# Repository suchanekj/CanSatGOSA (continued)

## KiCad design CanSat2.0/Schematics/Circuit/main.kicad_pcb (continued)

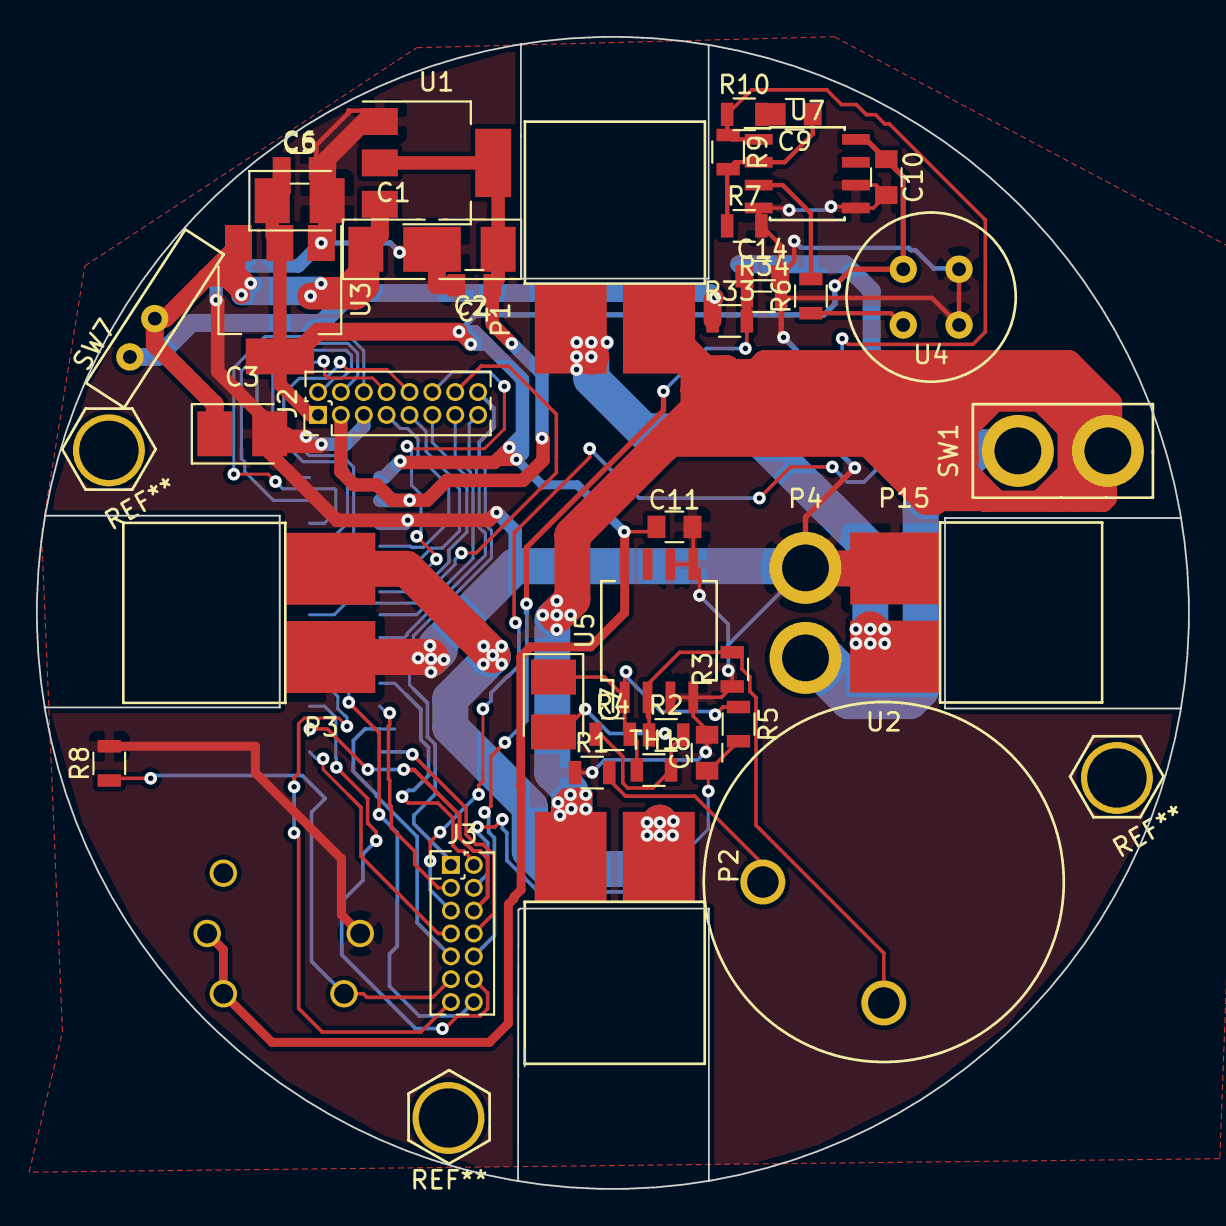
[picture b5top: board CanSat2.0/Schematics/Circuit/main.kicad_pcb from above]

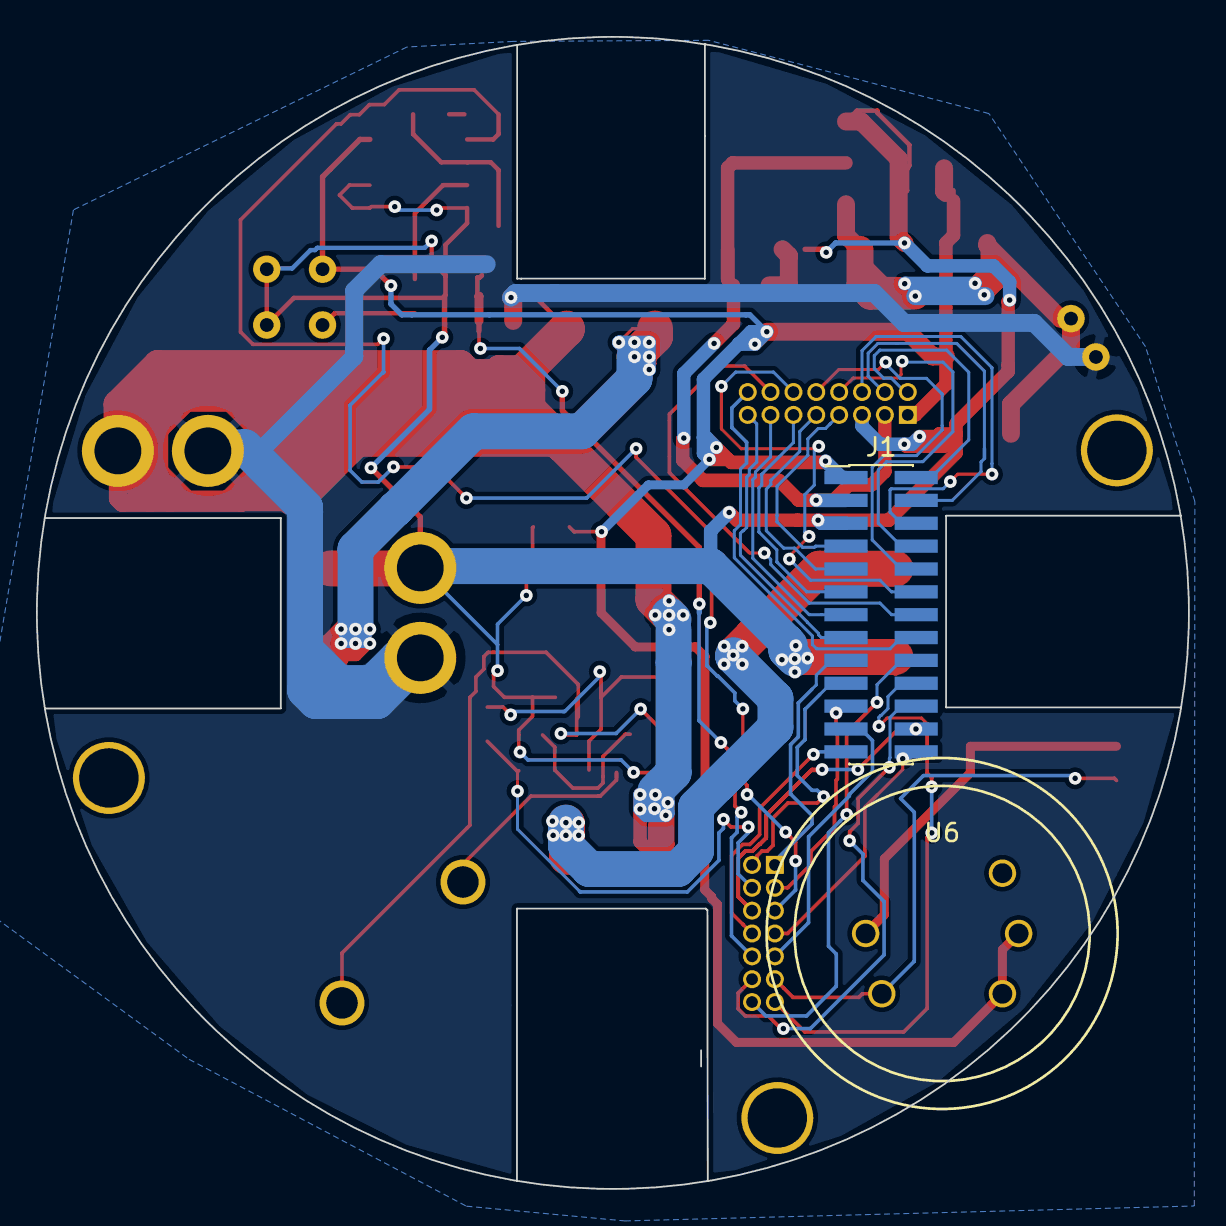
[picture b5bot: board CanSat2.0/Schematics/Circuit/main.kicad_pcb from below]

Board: 2 copper layers, 64.0 x 64.0 mm, 42 parts (2 on the bottom side), 43 nets.

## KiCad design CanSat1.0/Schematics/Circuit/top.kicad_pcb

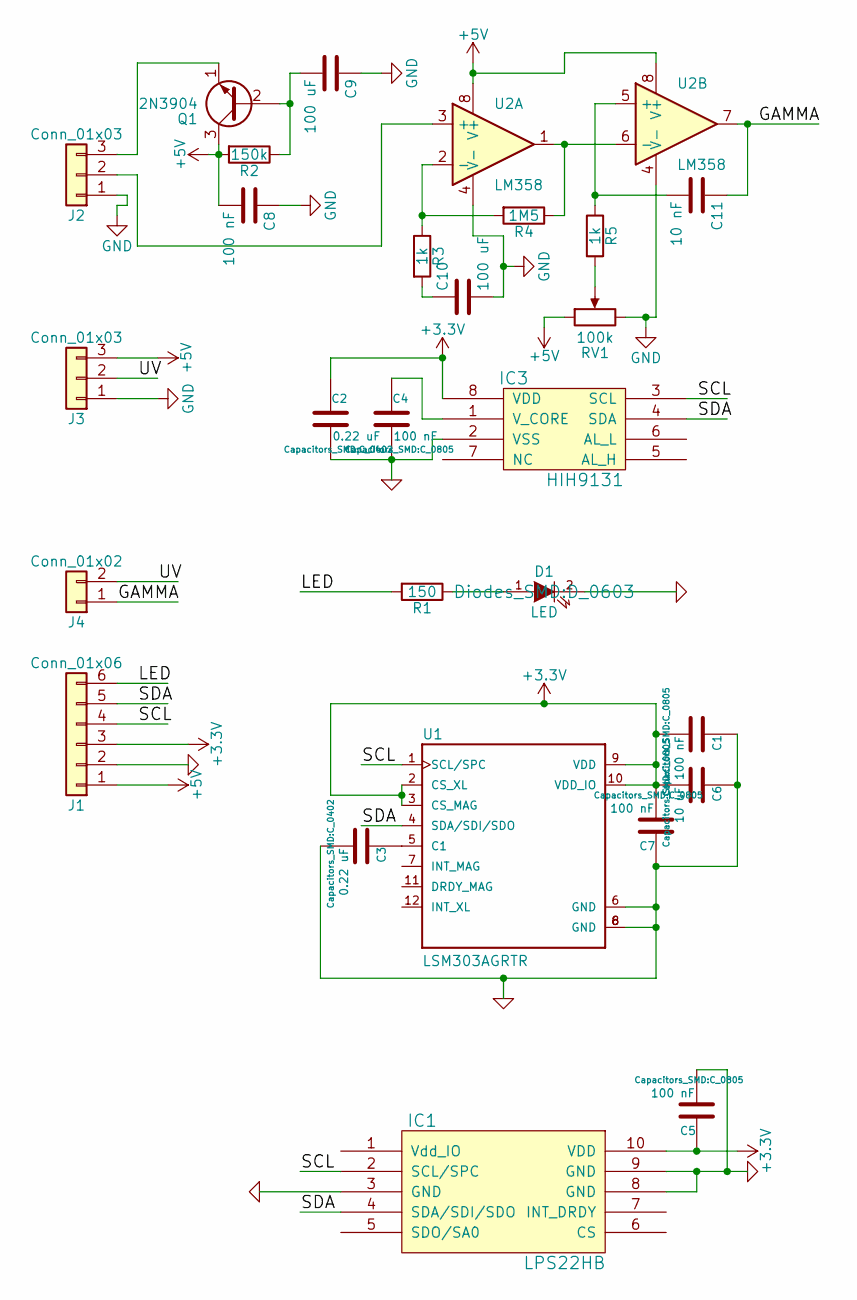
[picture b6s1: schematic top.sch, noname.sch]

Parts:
C1, C4, C5, C7, C8: 100 nF; C_0805
C2, C3: 0.22 uF; C_0402
C6: 10 uF; C_0805
C9, C10: 100 uF; CP_Tantalum_Case-A_EIA-3216-18_Reflow
C11: 10 nF; C_0603
D1: LED; D_0603
IC1: LPS22HB; LGA10R50P2X3_200X200X80
IC3: HIH9131; SOIC127P600X175-8N
J1: Conn_01x06; Pin_Header_Straight_1x06_Pitch1.27mm_SMD_Pin1Left
J2: Conn_01x03; MOLEX_PicoBlade_3
J3: Conn_01x03; Pin_Header_Straight_1x03_Pitch2.54mm
J4: Conn_01x02; MOLEX_PicoBlade_2
Q1: 2N3904; TO-92_Molded_Narrow
R1: 150; R_0805
R2: 150k; R_0603
R3, R5: 1k; R_0603
R4: 1M5; R_0603
RV1: 100k; Pin_Header_Straight_1x03_Pitch2.54mm
U1: LSM303AGRTR
U2: LM358; SOIC127P600X175-8N

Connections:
+3V3: C1.2, C2.1, C5.1, C6.2, C7.2, IC1.10 (VDD), IC3.8 (VDD), J1.3, U1.2 (CS_XL), U1.3 (CS_MAG), U1.9 (VDD), U1.10 (VDD_IO)
+5V: C8.2, J1.1, J3.3, Q1.3 (C), R2.2, RV1.1, U2.8 (V+)
/GAMMA: C11.1, J4.1, U2.7
/LED: J1.6, R1.2
/SCL: IC1.2 (SCL/SPC), IC3.3 (SCL), J1.4, U1.1 (SCL/SPC)
/SDA: IC1.4 (SDA/SDI/SDO), IC3.4 (SDA), J1.5, U1.4 (SDA/SDI/SDO)
/UV: J3.2, J4.2
GND: C1.1, C2.2, C3.2, C4.2, C5.2, C6.1, C7.1, C8.1, C9.1, C10.2, D1.2 (K), IC1.3 (GND), IC1.8 (GND), IC1.9 (GND), IC3.2 (VSS), J1.2, J2.1, J3.1, RV1.3, U1.6 (GND), U1.8 (GND), U2.4 (V-)
unnamed: C3.1, U1.5 (C1)
unnamed: C4.1, IC3.1 (V_CORE)
unnamed: C9.2, Q1.2 (B), R2.1
unnamed: C10.1, R3.2
unnamed: C11.2, R5.1, U2.5 (+)
unnamed: D1.1 (A), R1.1
unnamed: J2.2, U2.3 (+)
unnamed: J2.3, Q1.1 (E)
unnamed: R3.1, R4.2, U2.2 (-)
unnamed: R4.1, U2.1, U2.6 (-)
unnamed: R5.2, RV1.2

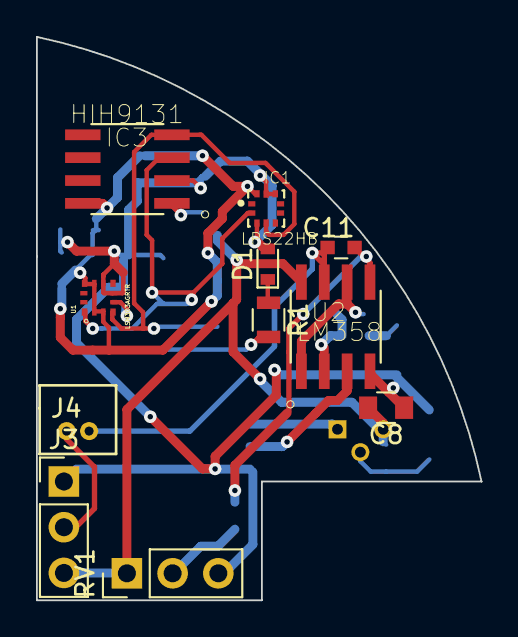
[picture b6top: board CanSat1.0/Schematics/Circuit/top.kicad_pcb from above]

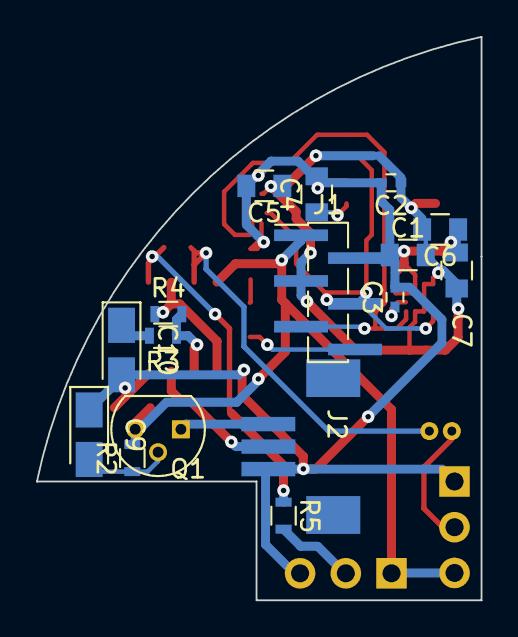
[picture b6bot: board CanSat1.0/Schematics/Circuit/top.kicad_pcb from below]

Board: 2 copper layers, 24.7 x 31.3 mm, 27 parts (16 on the bottom side), 19 nets.

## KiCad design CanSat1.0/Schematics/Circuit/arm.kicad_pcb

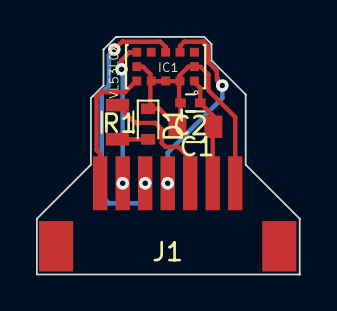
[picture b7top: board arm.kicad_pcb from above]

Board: 2 copper layers, 14.6 x 13.2 mm, 6 parts (0 on the bottom side), 8 nets.

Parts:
C1: 100nF; C_0805
C2: 4.7uF; C_0402
D1: LED; D_0603
IC1: VL53L0X; XDCR_VL53L0CXV0DH%2f1
J1: Conn_01x07; MOLEX_PicoBlade_7
R1: 150; R_0805

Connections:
+3V3: C1.1, C2.1, IC1.1, J1.6
/INT: IC1.7, J1.2
/LED: J1.5, R1.2
/SCL: IC1.10, J1.4
/SDA: IC1.9, J1.3
/XSHUT: IC1.5, J1.1
GND: C1.2, C2.2, D1.1, IC1.2, IC1.3, IC1.4, IC1.6, IC1.12, J1.7
unnamed: D1.2, R1.1

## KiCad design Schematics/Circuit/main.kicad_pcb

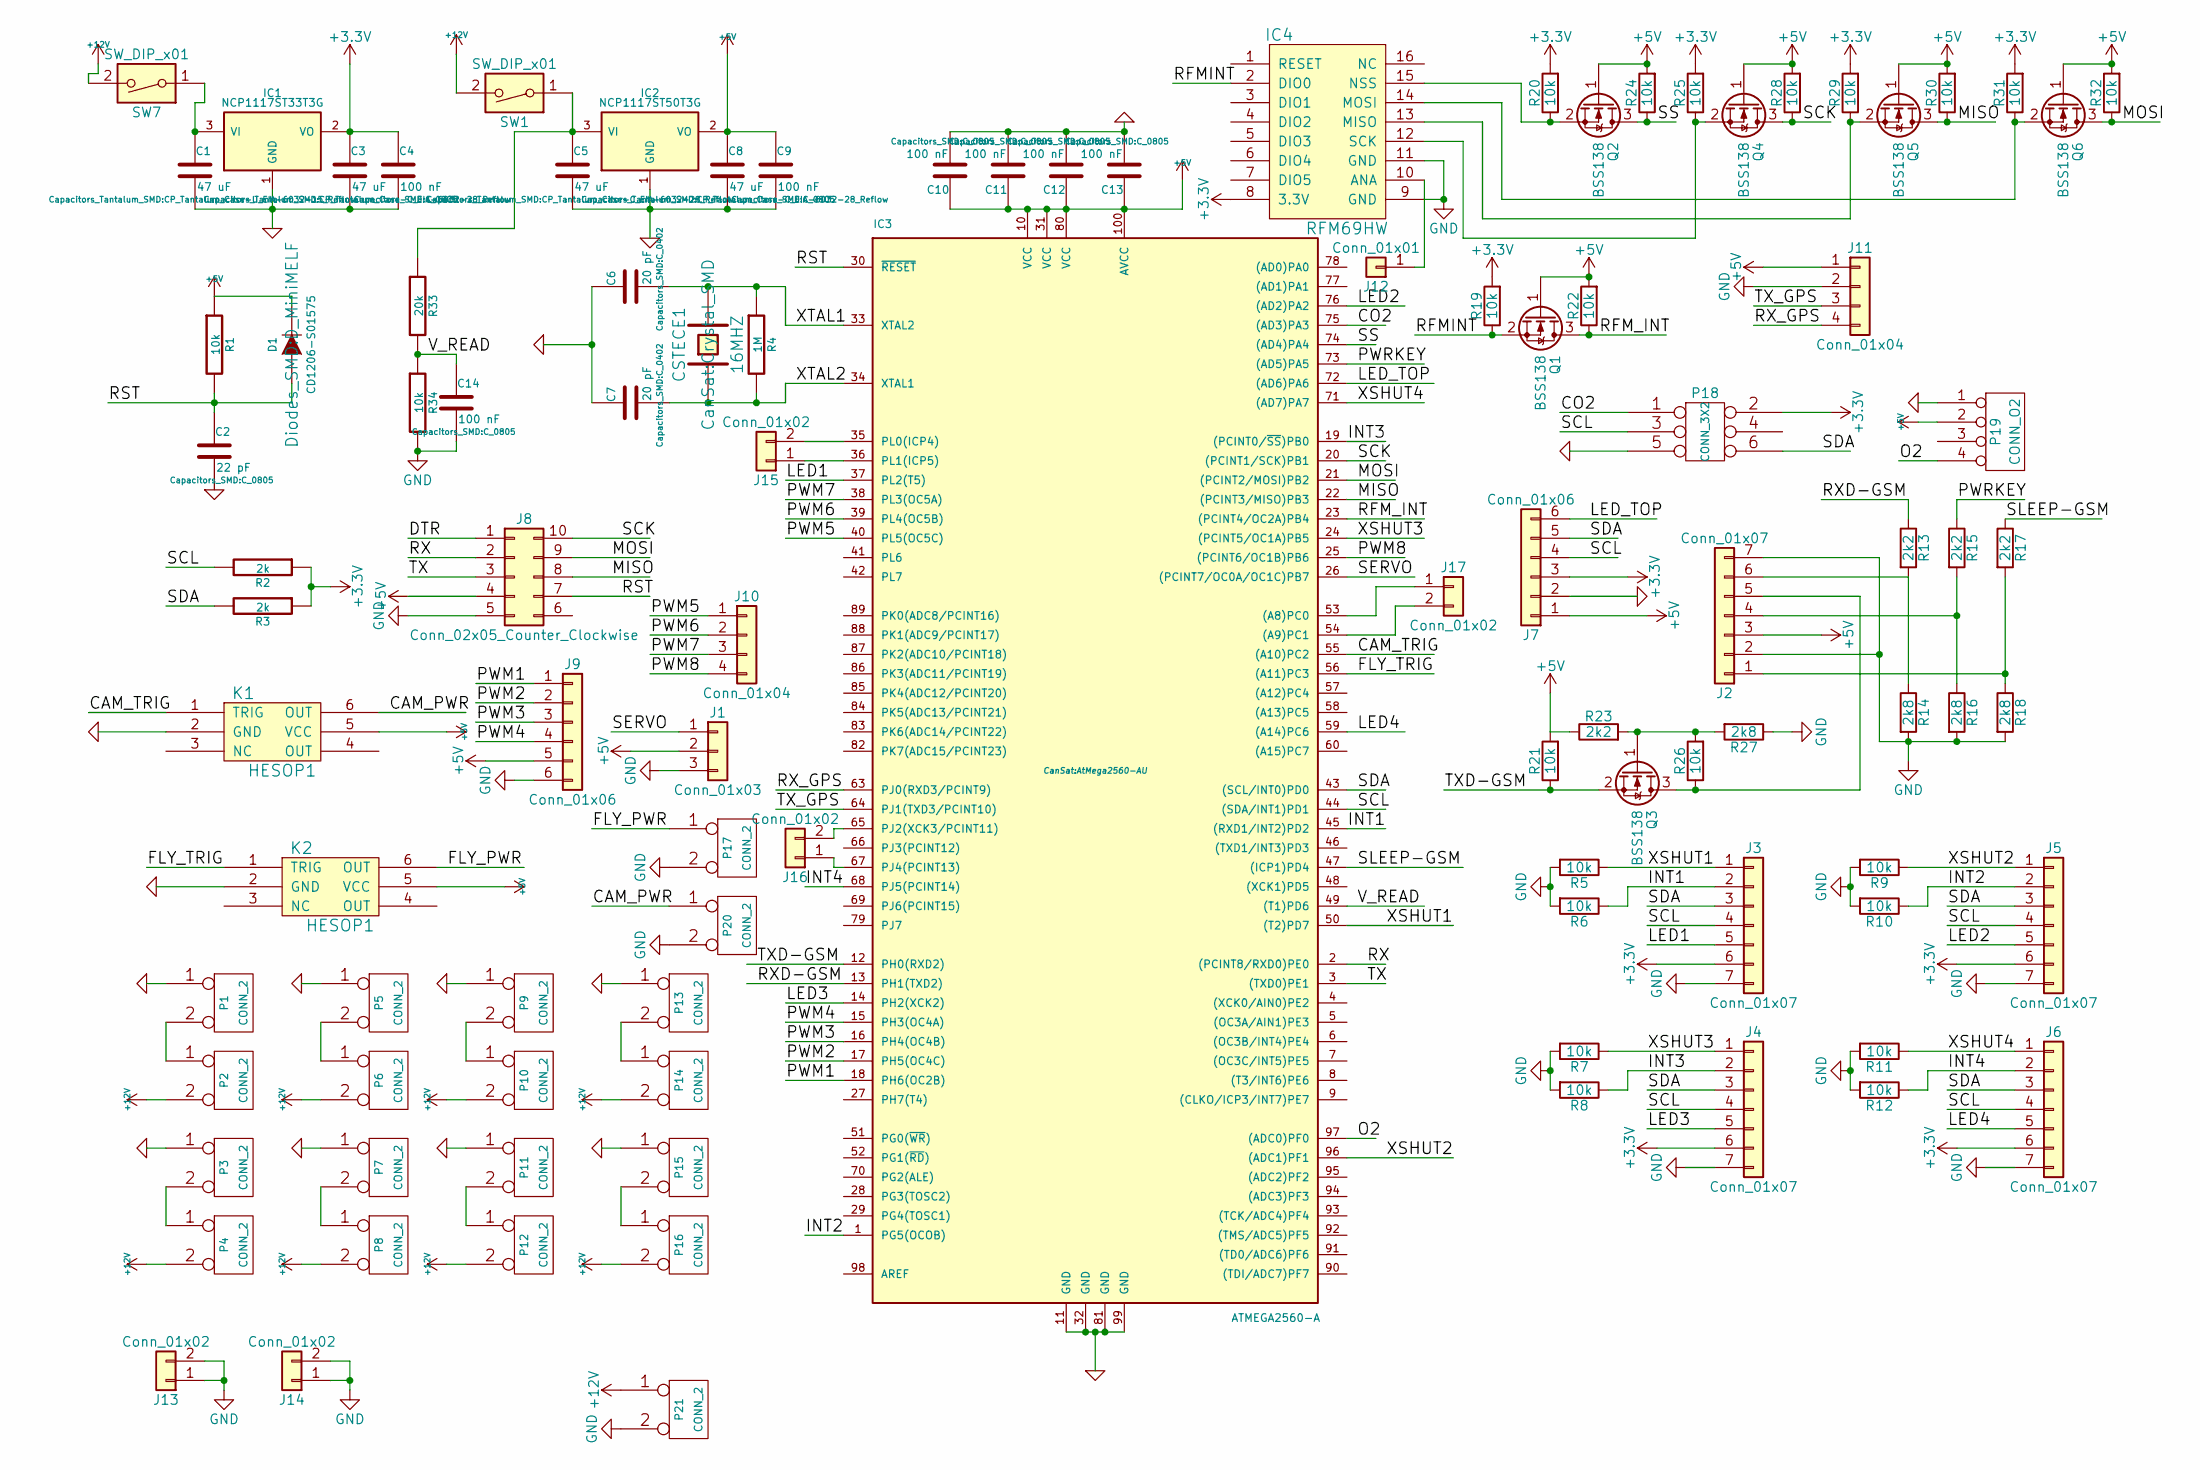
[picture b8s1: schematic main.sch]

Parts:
C1: 47 uF; CP_Tantalum_Case-U_EIA-6032-15_Reflow
C2: 22 pF; C_0805
C3, C5, C8: 47 uF; CP_Tantalum_Case-C_EIA-6032-28_Reflow
C4, C9, C10, C11, C12, C13, C14: 100 nF; C_0805
C6, C7: 20 pF; C_0402
CSTECE1: 16MHZ; Crystal_SMD
D1: CD1206-S01575; D_MiniMELF
IC1: NCP1117ST33T3G; ncp1117
IC2: NCP1117ST50T3G; ncp1117
IC3: ATMEGA2560-A; AtMega2560-AU
IC4: RFM69HW; XCVR_RFM95W-868S2
J1: Conn_01x03; MOLEX_0532610371
J2, J3, J4, J5, J6: Conn_01x07; MOLEX_PicoBlade_7
J7: Conn_01x06; Pin_Header_Straight_1x06_Pitch1.27mm_SMD_Pin1Left
J8: Conn_02x05_Counter_Clockwise; Pin_Header_Straight_2x05_Pitch1.00mm_SMD
J9: Conn_01x06; MOLEX_PicoBlade_6
J10, J11: Conn_01x04; MOLEX_PicoBlade_4
J12: Conn_01x01; Pin_Header_Straight_1x01_Pitch2.54mm
J13, J14, J15, J16, J17: Conn_01x02; MOLEX_PicoBlade_2
K1, K2: HESOP1; SMD_6pin_IC
P1, P2, P3, P4, P5, P6, P7, P8, P9, P10, P11, P12, P13, P14, P15, P16, P17, P20, P21: CONN_2; MOLEX_PicoBlade_2
P18: CONN_3X2; co2
P19: CONN_O2; MOLEX_PicoBlade_4
Q1, Q2, Q3, Q4, Q5, Q6: BSS138; SOT-23
R1, R5, R6, R7, R8, R9, R10, R11, R12, R19, R20, R21, R22, R24, R25, R26, R28, R29, R30, R31, R32, R34: 10k; R_0603
R2, R3: 2k; R_0603
R4: 1M; R_0603
R13, R15, R17, R23: 2k2; R_0805
R14, R16, R18, R27: 2k8; R_0603
R33: 20k; R_0603
SW1, SW7: SW_DIP_x01; Switch

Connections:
+3V3: C3.1, C4.1, IC1.2 (VO), IC4.8 (3.3V), J3.6, J4.6, J5.6, J6.6, J7.3, P18.2, R2.1, R3.1, R19.2, R20.2, R25.2, R29.2, R31.2
+5V: C8.1, C9.1, C10.1, C11.1, C12.1, C13.1, D1.2 (K), IC2.2 (VO), IC3.10 (VCC), IC3.31 (VCC), IC3.80 (VCC), IC3.100 (AVCC), J1.2, J2.3, J7.1, J8.4, J9.5, J11.1, K1.5 (VCC), K2.5 (VCC), P19.2, Q1.1 (G), Q2.1 (G), Q4.1 (G), Q5.1 (G), Q6.1 (G), R1.1, R21.2, R22.2, R23.1, R24.2, R28.2, R30.2, R32.2
+12V: P2.2 (PM), P4.2 (PM), P6.2 (PM), P8.2 (PM), P10.2 (PM), P12.2 (PM), P14.2 (PM), P16.2 (PM), P21.1, SW1.2, SW7.2
/CAM_PWR: K1.6 (OUT), P20.1
/CAM_TRIG: IC3.55 ((A10)PC2), K1.1 (TRIG)
/CO2: IC3.75 ((AD3)PA3), P18.1
/DTR: J8.1
/FLY_PWR: K2.6 (OUT), P17.1
/FLY_TRIG: IC3.56 ((A11)PC3), K2.1 (TRIG)
/INT1: IC3.45 ((RXD1/INT2)PD2), J3.2, R6.1
/INT2: IC3.1 (PG5(OCOB)), J5.2, R10.1
/INT3: IC3.19 ((PCINT0/~SS~)PB0), J4.2, R8.1
/INT4: IC3.68 (PJ5(PCINT14)), J6.2, R12.1
/LED1: IC3.37 (PL2(T5)), J3.5
/LED2: IC3.76 ((AD2)PA2), J5.5
/LED3: IC3.14 (PH2(XCK2)), J4.5
/LED4: IC3.59 ((A14)PC6), J6.5
/LED_TOP: IC3.72 ((AD6)PA6), J7.6
/MISO: IC3.22 ((PCINT3/MISO)PB3), J8.8, Q5.3 (D), R30.1
/MOSI: IC3.21 ((PCINT2/MOSI)PB2), J8.9, Q6.3 (D), R32.1
/O2: IC3.97 ((ADC0)PF0), P19.4
/PWM1: IC3.18 (PH6(OC2B)), J9.1
/PWM2: IC3.17 (PH5(OC4C)), J9.2
/PWM3: IC3.16 (PH4(OC4B)), J9.3
/PWM4: IC3.15 (PH3(OC4A)), J9.4
/PWM5: IC3.40 (PL5(OC5C)), J10.1
/PWM6: IC3.39 (PL4(OC5B)), J10.2
/PWM7: IC3.38 (PL3(OC5A)), J10.3
/PWM8: IC3.25 ((PCINT6/OC1B)PB6), J10.4
/PWRKEY: IC3.73 ((AD5)PA5), R15.1
/RFMINT: IC4.2 (DIO0), Q1.2 (S), R19.1
/RFM_INT: IC3.23 ((PCINT4/OC2A)PB4), Q1.3 (D), R22.1
/RST: C2.1, D1.1 (A), IC3.30 (~RESET), J8.7, R1.2
/RX: IC3.2 ((PCINT8/RXD0)PE0), J8.2
/RXD-GSM: IC3.13 (PH1(TXD2)), R13.1
/RX_GPS: IC3.63 (PJ0(RXD3/PCINT9)), J11.4
/SCK: IC3.20 ((PCINT1/SCK)PB1), J8.10, Q4.3 (D), R28.1
/SCL: IC3.44 ((SDA/INT1)PD1), J3.4, J4.4, J5.4, J6.4, J7.4, P18.3, R2.2
/SDA: IC3.43 ((SCL/INT0)PD0), J3.3, J4.3, J5.3, J6.3, J7.5, P18.6, R3.2
/SERVO: IC3.26 ((PCINT7/OC0A/OC1C)PB7), J1.1
/SLEEP-GSM: IC3.47 ((ICP1)PD4), R17.1
/SS: IC3.74 ((AD4)PA4), Q2.3 (D), R24.1
/TX: IC3.3 ((TXD0)PE1), J8.3
/TXD-GSM: IC3.12 (PH0(RXD2)), Q3.2 (S), R21.1
/TX_GPS: IC3.64 (PJ1(TXD3/PCINT10)), J11.3
/V_READ: C14.1, IC3.49 ((T1)PD6), R33.2, R34.1
/XSHUT1: IC3.50 ((T2)PD7), J3.1, R5.1
/XSHUT2: IC3.96 ((ADC1)PF1), J5.1, R9.1
/XSHUT3: IC3.24 ((PCINT5/OC1A)PB5), J4.1, R7.1
/XSHUT4: IC3.71 ((AD7)PA7), J6.1, R11.1
/XTAL1: C6.2, CSTECE1.2, IC3.33 (XTAL2), R4.1
/XTAL2: C7.2, CSTECE1.1, IC3.34 (XTAL1), R4.2
GND: C1.2, C2.2, C3.2, C4.2, C5.2, C6.1, C7.1, C8.2, C9.2, C10.2, C11.2, C12.2, C13.2, C14.2, IC1.1 (GND), IC2.1 (GND), IC3.11 (GND), IC3.32 (GND), IC3.81 (GND), IC3.99 (GND), IC4.9 (GND), IC4.11 (GND), J1.3, J2.2, J2.7, J3.7, J4.7, J5.7, J6.7, J7.2, J8.5, J9.6, J11.2, J13.1, J13.2, J14.1, J14.2, K1.2 (GND), K2.2 (GND), P1.1, P3.1, P5.1, P7.1, P9.1, P11.1, P13.1, P15.1, P17.2 (PM), P18.5, P19.1, P20.2 (PM), P21.2 (PM), R5.2, R6.2, R7.2, R8.2, R9.2, R10.2, R11.2, R12.2, R14.2, R16.2, R18.2, R27.1, R34.2
unnamed: C1.1, IC1.3 (VI), SW7.1
unnamed: C5.1, IC2.3 (VI), R33.1, SW1.1
unnamed: IC3.35 (PL0(ICP4)), J15.2
unnamed: IC3.36 (PL1(ICP5)), J15.1
unnamed: IC3.53 ((A8)PC0), J17.1
unnamed: IC3.54 ((A9)PC1), J17.2
unnamed: IC3.65 (PJ2(XCK3/PCINT11)), J16.2
unnamed: IC3.67 (PJ4(PCINT13)), J16.1
unnamed: IC4.10 (ANA), J12.1
unnamed: IC4.12 (SCK), Q4.2 (S), R25.1
unnamed: IC4.13 (MISO), Q5.2 (S), R29.1
unnamed: IC4.14 (MOSI), Q6.2 (S), R31.1
unnamed: IC4.15 (NSS), Q2.2 (S), R20.1
unnamed: J2.1, R17.2, R18.1
unnamed: J2.4, R15.2, R16.1
unnamed: J2.5, Q3.3 (D), R26.1
unnamed: J2.6, R13.2, R14.1
unnamed: P1.2 (PM), P2.1
unnamed: P3.2 (PM), P4.1
unnamed: P5.2 (PM), P6.1
unnamed: P7.2 (PM), P8.1
unnamed: P9.2 (PM), P10.1
unnamed: P11.2 (PM), P12.1
unnamed: P13.2 (PM), P14.1
unnamed: P15.2 (PM), P16.1
unnamed: Q3.1 (G), R23.2, R26.2, R27.2

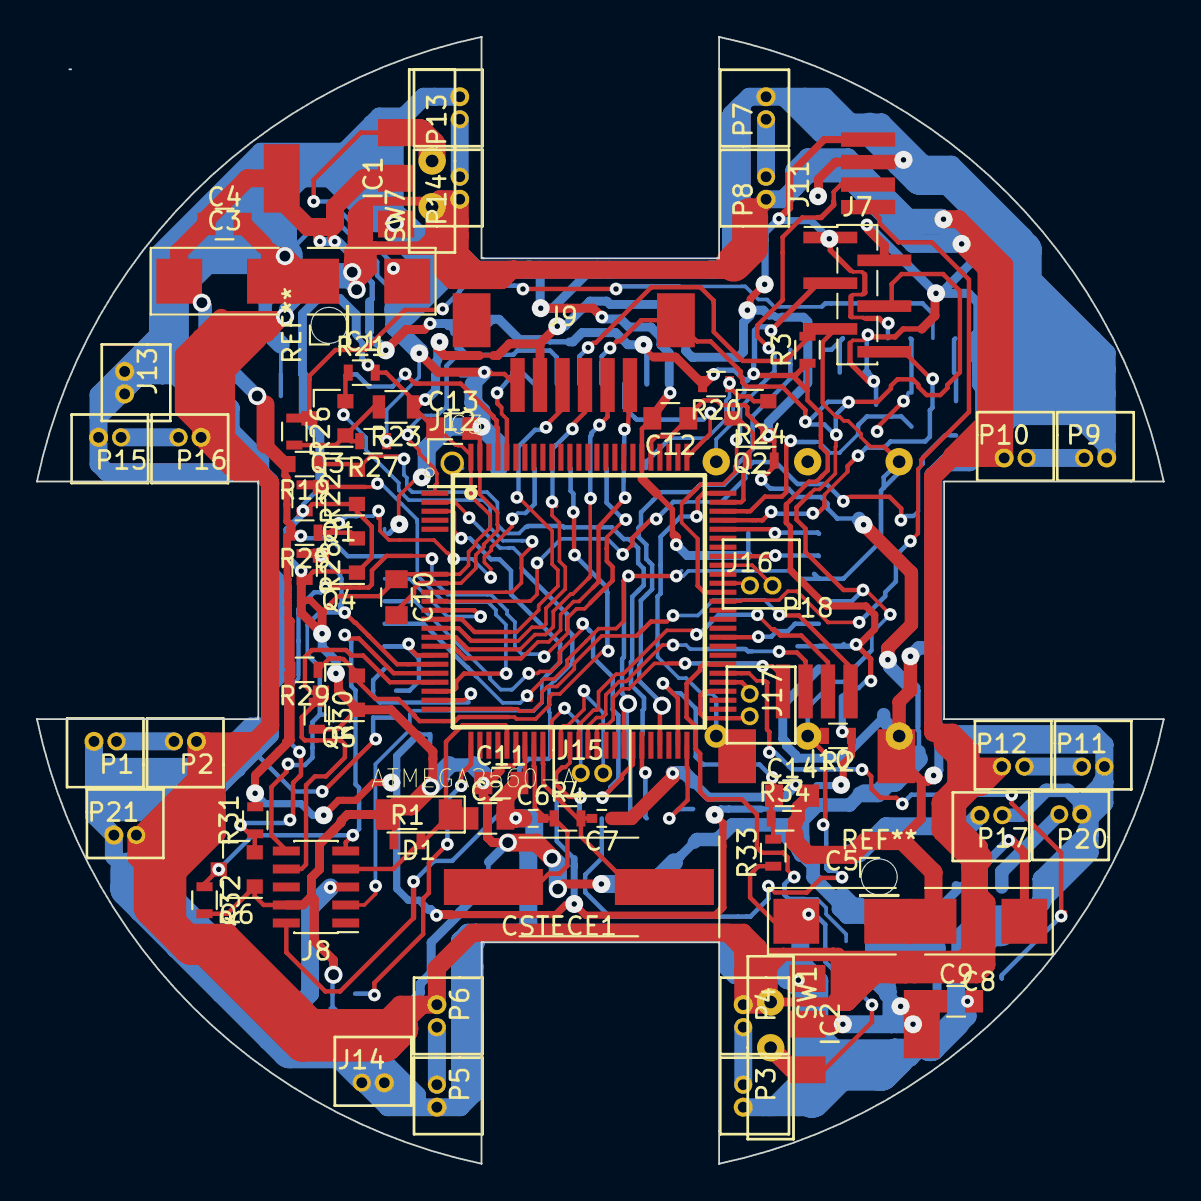
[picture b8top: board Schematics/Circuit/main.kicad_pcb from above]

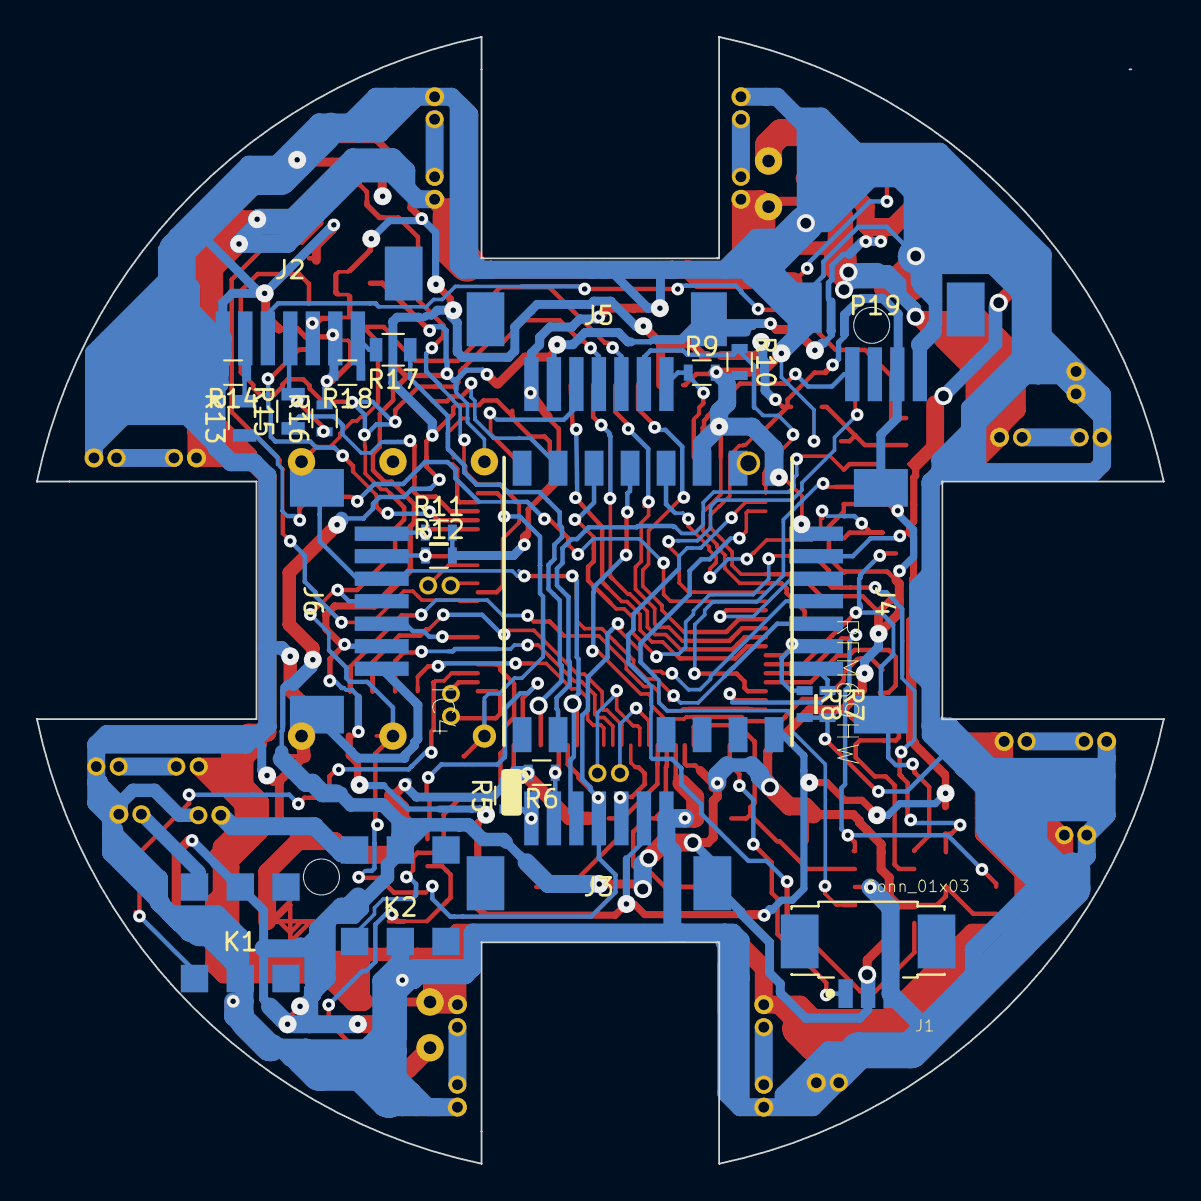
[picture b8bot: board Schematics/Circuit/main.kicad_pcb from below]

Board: 2 copper layers, 62.6 x 62.6 mm, 102 parts (24 on the bottom side), 78 nets.

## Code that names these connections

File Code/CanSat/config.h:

/*
  CanSat GOSA
  Code for a tiny probe to investigate existance of life
  Copyright (C) 2018  Jakub Suchánek, suchanek989@seznam.cz
  http://github.com/suchanekj/CanSatGOSA

  License
  **********************************************************************************
  This program is free software; you can redistribute it
  and/or modify it under the terms of the GNU General
  Public License as published by the Free Software
  Foundation; either version 3 of the License, or
  (at your option) any later version.

  This program is distributed in the hope that it will
  be useful, but WITHOUT ANY WARRANTY; without even the
  implied warranty of MERCHANTABILITY or FITNESS FOR A
  PARTICULAR PURPOSE. See the GNU General Public
  License for more details.

  You should have received a copy of the GNU General
  Public License along with this program.
  If not, see <http://www.gnu.org/licenses/>.

  Licence can be viewed at
  https://github.com/suchanekj/CanSatGOSA/blob/master/LICENSE

  Please maintain this license information along with authorship
  and copyright notices in any redistribution of this code
  **********************************************************************************
*/

#ifndef CANSAT_CONFIG_H
#define CANSAT_CONFIG_H

/*
 ***********************************************************************************
 *  Landing spot
 */

#define DESTINATION_LAT 499951500
#define DESTINATION_LON 145513150
#define DESTINATION_ALT 41500

#define EARTH_RADIUS_M 6371009
#define RAD_PER_DEGREE (PI / 180.0)
#define STARTING_ALT 41500
/*
 ***********************************************************************************
 *  Subsystem definitions
 */
//comment any line to disable subsystem

#define DEBUG
#define BAROMETER
#define RADIO
//#define HUMIDITY_SENSOR
#define RANGING_SENSOR
#define COMPASS
//#define GSM
#define GPS

/*
 ***********************************************************************************
 *  Parameter definitions
 */

//Transmitting

#define USE_RADIO 1
#define USE_EMAIL 0
#define USE_SMS   0

//Radio Parameters

#define NODEID        2    //unique for each node on same network
#define NETWORKID     42  //the same on all nodes that talk to each other
#define GATEWAYID     1    //Receiving node
#define ENCRYPTKEY    "Suchy Na Mars!!!" //exactly the same 16 characters/bytes on all nodes!

//GSM parameters

#define GSM_WAIT_FOR_POWER_UP 10000

/*
 ***********************************************************************************
 *  Port definitions
 */

//debugging

#define DEBUG_SERIAL Serial

//PWM output to Flight Controller

#define FC_PWM_1 6
#define FC_PWM_2 7
#define FC_PWM_3 46
#define FC_PWM_4 12
#define FC_PWM_5 8
#define FC_PWM_6 9
#define FC_PWM_7 45
#define FC_PWM_8 44

//Arms

const int ARM_LED[4] = {47, 24, 76, 31};
const int ARM_RANGING_XSHUT[4] = {38, 55, 11, 29};
const int ARM_RANGING_INTERRUPT[4] = {19, 4, 53, 73};

//Top board

#define TOP_LED 28

//GSM module

#define GSM_SERIAL Serial2
#define GSM_SLEEP 83
#define GSM_POWER_KEY 27

//GPS module

#define GPS_SERIAL Serial1
//#define gpsPort Serial1
//#define GPS_PORT_NAME "Serial1"

//Servo

#define SERVO 13

//O2 sensor

#define O2 A0

//CO2 sensor

#define CO2 25

//Camera power

#define CAMERA_POWER 35

//Flight Controller power

#define FC_POWER 34

//Radio transmitter

#define RFM_INT 10
#define RFM_SS 26

//Read battery voltage

#define BATTERY_VOLTAGE A8

//UV read

#define UV A6

//Gamma read

#define GAMMA


#endif //CANSAT_CONFIG_H

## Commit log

2017-11-15 Add radio Hello world!
2017-11-30 added basic circuit schematic
2017-12-14 Create LICENSE
2017-12-28 Add first part of the model
2017-12-31 Add drone parts model
2018-01-04 Edit schematic
2018-01-06 Edit schematic and model
2018-01-08 Edit schematic and footprints
2018-01-16 Edit finish circuits and some model work
2018-01-16 Edit pcb and model
2018-01-17 Edit, add overall schematic, widen gaps in pcb
2018-01-20 Edit power port distribution
2018-02-02 Edit schematic and model, add images
2018-02-02 Add GPS support
2018-02-17 Add UV and Gamma detection, fix main pcb
2018-03-10 Edit arm conection in model
2018-03-10 add new version of HULL
2018-03-11 Add arm holders
2018-03-12 Add modular version of hull
2018-03-15 Fix arm holes in bottom hull
2018-03-17 Add camera to assembly and reorganize scraper
2018-03-17 Edit model - finalizing the assembly, all components fit
2018-03-17 Add servo holders in model
2018-03-21 Add stabilization holders for flight controler
2018-04-01 Add base and libraries for final code
2018-04-01 Add main schematic export
2018-04-01 add brackets to encapsulate data
2018-04-01 Add new schematic and pcb exports
2018-04-01 Add sending data to web
2018-04-03 add pictures
2018-04-03 rename files
2018-04-04 add logo
2018-04-04 Add body of the CanSat code, needs to be tested
2018-04-11 edit parsing and other
2018-04-12 add final report
2018-04-15 Edit arduino code
2018-04-17 Edit code - sensors functioning, add printable schematics
2018-04-19 edit some main code updates
2018-04-19 edit parsing
2018-04-19 Add final edits
2018-04-22 Edit final code for national finals
2018-05-03 Add base for CanSat HATALOM 2.0
2018-05-07 Edite upper part of model
2018-05-10 PCBs
2018-05-10 Add new camera in model
2018-05-25 Add three top boards and some other circuitry and modelling
2018-05-28 Add new pcbs - center and bottom - and fill the lower half of the model
2018-06-01 Middle-conectors
2018-06-03 Hull-component holders 1/2
    Cameras and gamma are not finished yet
2018-06-03 add gamma - collides with motors
2018-06-03 pillar4 - nethole
2018-06-03 Edit final version of pcbs, gerbers generated
2018-06-04 nearly final
2018-06-04 vazby
2018-06-10 Edit model - hull pillars edited to hold most components
2018-06-10 Add presentation view of the model and edit hull_main
2018-06-12 Edit model - add second camera position
2018-06-13 Add analysis spreadsheat
2018-06-19 Add printable schematics
2018-06-21 Edit code - add some new libraries
2018-06-21 Add new version code configs
2018-06-23 Edit GPS interrupt handling
2018-06-25 Add watchdog resetting
2018-06-27 Add files via upload
    Part of analysis focussed on atmospheric data.
2018-06-28 Edit main code, add examples, fix spectroscopy
2018-06-29 Last day edits T - 3 hours
2018-06-29 Last day edits T - 1 hours
2018-06-29 Add data
